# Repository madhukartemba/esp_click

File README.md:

# esp_click
This is a deep sleep ESP32 C6 push button device which transmits clicks via ESPNOW protocol. It uses an ESP32C6 microcontroller.

## Firmware build: broken RISC-V toolchain (PlatformIO)

ESP32-C6 uses the RISC-V toolchain (`riscv32-esp-elf-g++`). If the build fails with:

`sh: riscv32-esp-elf-g++: command not found` (exit 127)

the compiler package is missing, incomplete, or PlatformIO’s environment did not pick it up. From the firmware directory (`esp_click_firmware`), remove the toolchain and project build cache, then rebuild so PlatformIO re-downloads the toolchain:

```bash
cd esp_click_firmware
rm -rf .pio
rm -rf ~/.platformio/packages/toolchain-riscv32-esp
rm -rf ~/.platformio/tools/toolchain-riscv32-esp
pio run
```

Optional: remove all installed compiler packages (they reinstall on demand):

```bash
rm -rf ~/.platformio/packages/toolchain-*
```

Optional: prune unused PlatformIO packages:

```bash
pio system prune
```

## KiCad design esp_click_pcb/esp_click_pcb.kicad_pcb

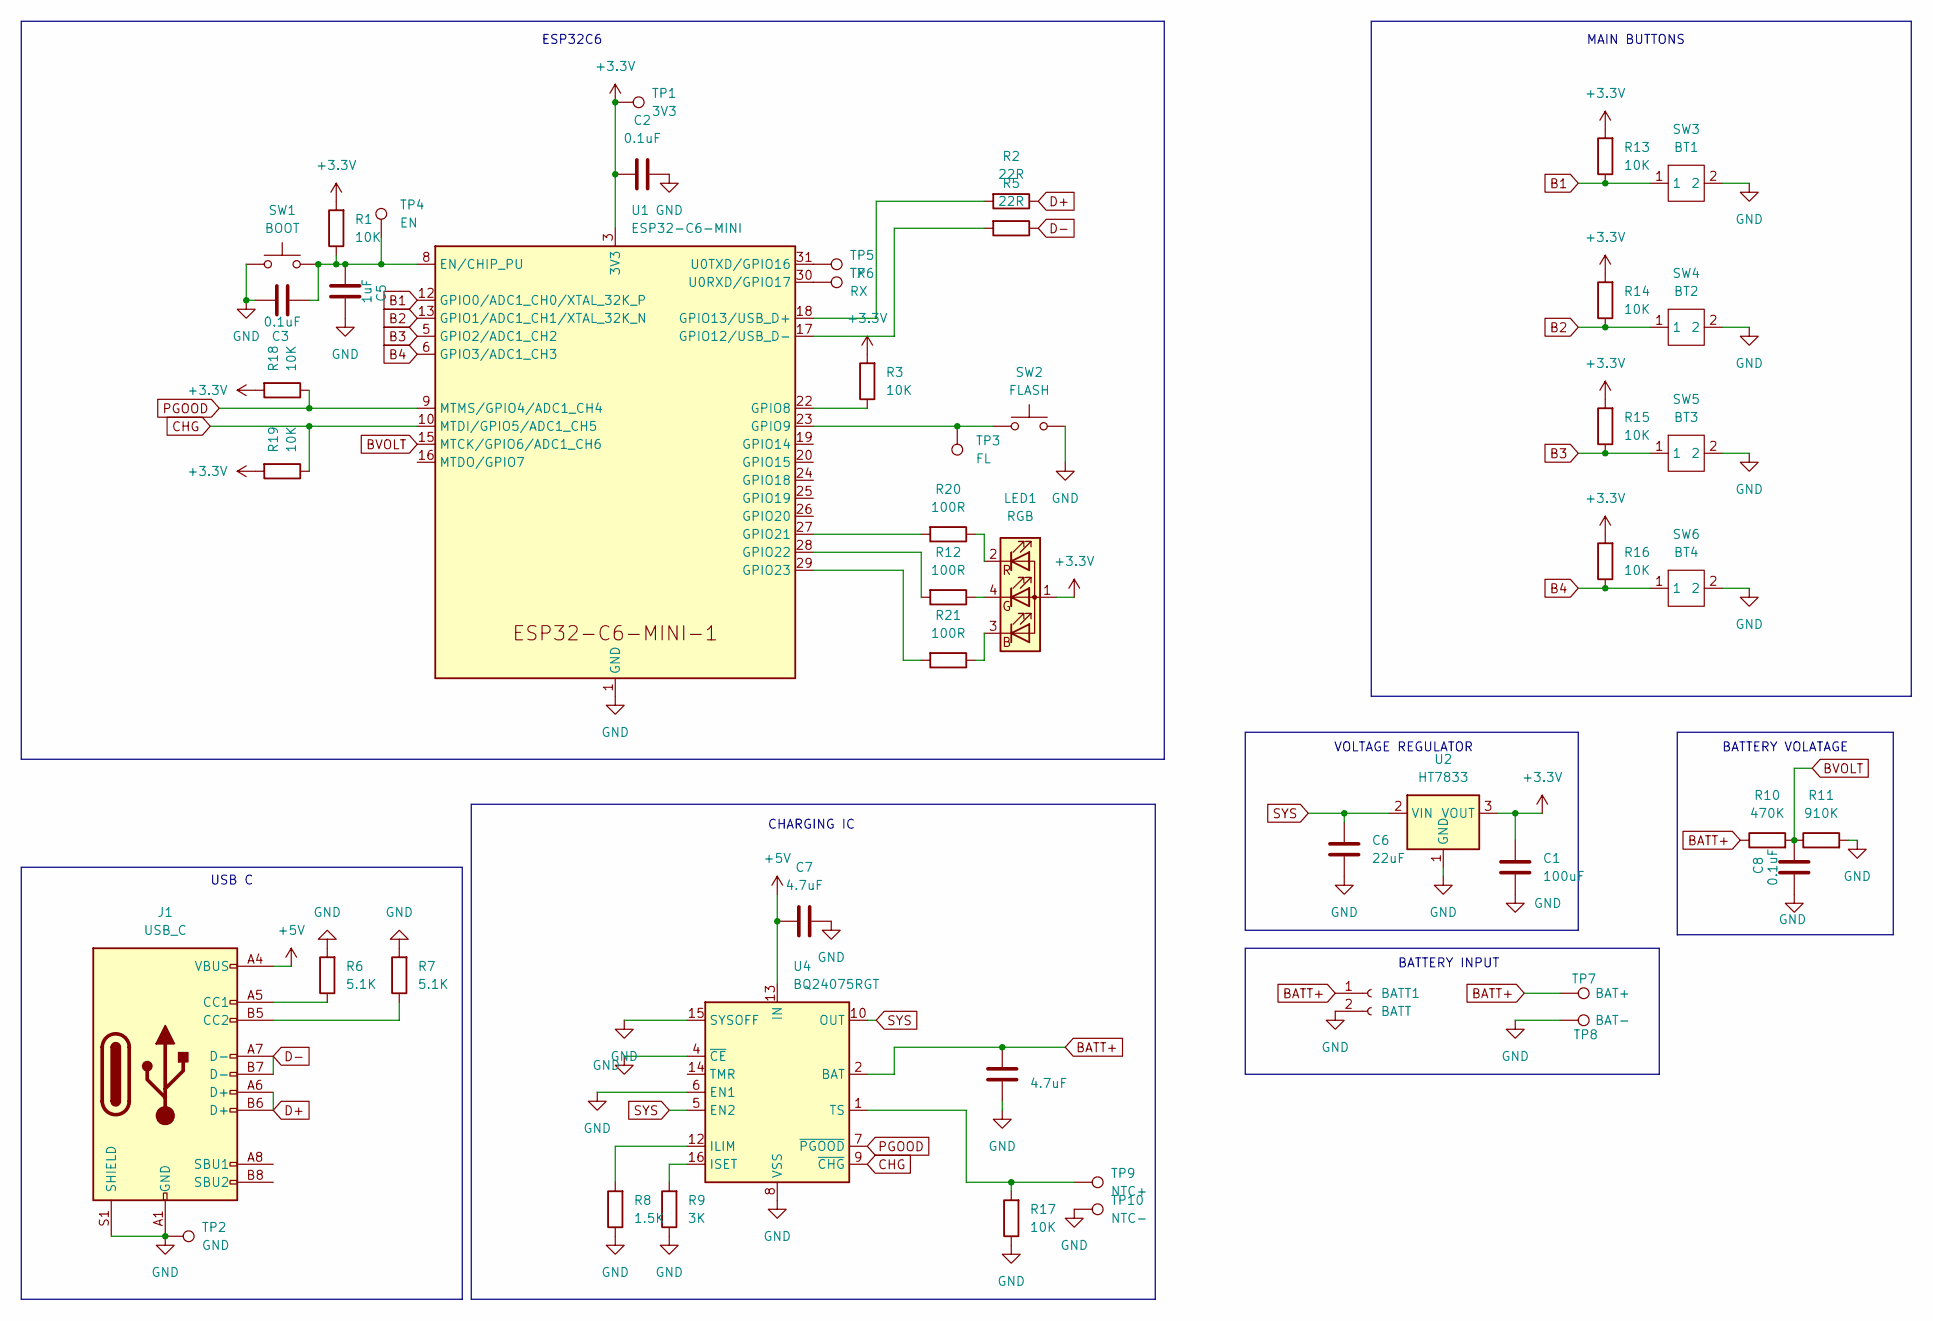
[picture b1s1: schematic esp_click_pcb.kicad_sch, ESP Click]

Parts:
BATT1: BATT; JST_SHL_SM02B-SHLS-TF_1x02-1MP_P1.00mm_Horizontal
C1: 100uF; C_0805_2012Metric
C2, C3, C8: 0.1uF; C_0603_1608Metric
C4, C7: 4.7uF; C_0805_2012Metric
C5: 1uF; C_0603_1608Metric
C6: 22uF; C_0805_2012Metric
J1: USB_C; USB_C_Receptacle_GCT_USB4110
LED1: RGB; XL-1615RGBC-RF
R1, R3, R13, R14, R15, R16, R17, R18, R19: 10K; R_0603_1608Metric
R2, R5: 22R; R_0603_1608Metric
R6, R7: 5.1K; R_0603_1608Metric
R8: 1.5K; R_0603_1608Metric
R9: 3K; R_0603_1608Metric
R10: 470K; R_0603_1608Metric
R11: 910K; R_0603_1608Metric
R12, R20, R21: 100R; R_0603_1608Metric
SW1: BOOT; TST-A002_0.6MM_BOSS
SW2: FLASH; TST-A002_0.6MM_BOSS
SW3: BT1; TS6643WS
SW4: BT2; TS6643WS
SW5: BT3; TS6643WS
SW6: BT4; TS6643WS
TP1: 3V3; TestPoint_Pad_D1.5mm
TP2: GND; TestPoint_Pad_D1.5mm
TP3: FL; TestPoint_Pad_D1.5mm
TP4: EN; TestPoint_Pad_D1.5mm
TP5: TX; TestPoint_Pad_D1.5mm
TP6: RX; TestPoint_Pad_D1.5mm
TP7: BAT+; TestPoint_Pad_D2.0mm
TP8: BAT-; TestPoint_Pad_D2.0mm
TP9: NTC+; TestPoint_Pad_D1.5mm
TP10: NTC-; TestPoint_Pad_D1.5mm
U1: ESP32-C6-MINI; ESP32-C6-MINI-1
U2: HT7833; SOT-89-3
U4: BQ24075RGT; VQFN-16-1EP_3x3mm_P0.5mm_EP1.6x1.6mm

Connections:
+3.3V: C1.1, C2.1, LED1.1 (A), R1.2, R3.2, R13.2, R14.2, R15.2, R16.2, R18.2, R19.2, TP1.1, U1.3 (3V3), U2.3 (VOUT)
+5V: C7.1, J1.A4 (VBUS), J1.A9 (VBUS), J1.B4 (VBUS), J1.B9 (VBUS), U4.13 (IN)
B1: R13.1, SW3.1, U1.12 (GPIO0/ADC1_CH0/XTAL_32K_P)
B2: R14.1, SW4.1, U1.13 (GPIO1/ADC1_CH1/XTAL_32K_N)
B3: R15.1, SW5.1, U1.5 (GPIO2/ADC1_CH2)
B4: R16.1, SW6.1, U1.6 (GPIO3/ADC1_CH3)
BATT+: BATT1.1, C4.1, R10.1, TP7.1, U4.2 (BAT), U4.3 (BAT)
BVOLT: C8.2, R10.2, R11.1, U1.15 (MTCK/GPIO6/ADC1_CH6)
CHG: R19.1, U1.10 (MTDI/GPIO5/ADC1_CH5), U4.9 (~CHG)
D+: J1.A6 (D+), J1.B6 (D+), R2.1
D-: J1.A7 (D-), J1.B7 (D-), R5.1
GND: BATT1.2, C1.2, C2.2, C3.2, C4.2, C5.2, C6.2, C7.2, C8.1, J1.A1 (GND), J1.A12 (GND), J1.B1 (GND), J1.B12 (GND), J1.S1 (SHIELD), R6.2, R7.2, R8.1, R9.1, R11.2, R17.1, SW1.1, SW2.2, SW3.2, SW4.2, SW5.2, SW6.2, TP2.1, TP8.1, TP10.1, U1.1 (GND), U1.2 (GND), U1.11 (GND), U1.14 (GND), U1.36 (GND), U1.37 (GND), U1.38 (GND), U1.39 (GND), U1.40 (GND), U1.41 (GND), U1.42 (GND), U1.43 (GND), U1.44 (GND), U1.45 (GND), U1.46 (GND), U1.47 (GND), U1.48 (GND), U1.49 (GND), U1.50 (GND), U1.51 (GND), U1.52 (GND), U1.53 (GND), U2.1 (GND), U4.4 (~CE), U4.6 (EN1), U4.8 (VSS), U4.15 (SYSOFF), U4.17 (VSS)
unnamed: J1.A5 (CC1), R6.1
unnamed: J1.B5 (CC2), R7.1
unnamed: LED1.3 (BK), R21.1
unnamed: LED1.4 (GK), R12.1
unnamed: LED1.2 (RK), R20.1
unnamed: C3.1, C5.1, R1.1, SW1.2, TP4.1, U1.8 (EN/CHIP_PU)
unnamed: R3.1, U1.22 (GPIO8)
unnamed: SW2.1, TP3.1, U1.23 (GPIO9)
unnamed: R5.2, U1.17 (GPIO12/USB_D-)
unnamed: R2.2, U1.18 (GPIO13/USB_D+)
unnamed: R20.2, U1.27 (GPIO21)
unnamed: R12.2, U1.28 (GPIO22)
unnamed: R21.2, U1.29 (GPIO23)
unnamed: TP6.1, U1.30 (U0RXD/GPIO17)
unnamed: TP5.1, U1.31 (U0TXD/GPIO16)
unnamed: R8.2, U4.12 (ILIM)
unnamed: R9.2, U4.16 (ISET)
unnamed: R17.2, TP9.1, U4.1 (TS)
PGOOD: R18.1, U1.9 (MTMS/GPIO4/ADC1_CH4), U4.7 (~PGOOD)
SYS: C6.1, U2.2 (VIN), U4.5 (EN2), U4.10 (OUT), U4.11 (OUT)

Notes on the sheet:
MAIN BUTTONS
CHARGING IC
BATTERY VOLATAGE
USB C
BATTERY INPUT
VOLTAGE REGULATOR
ESP32C6

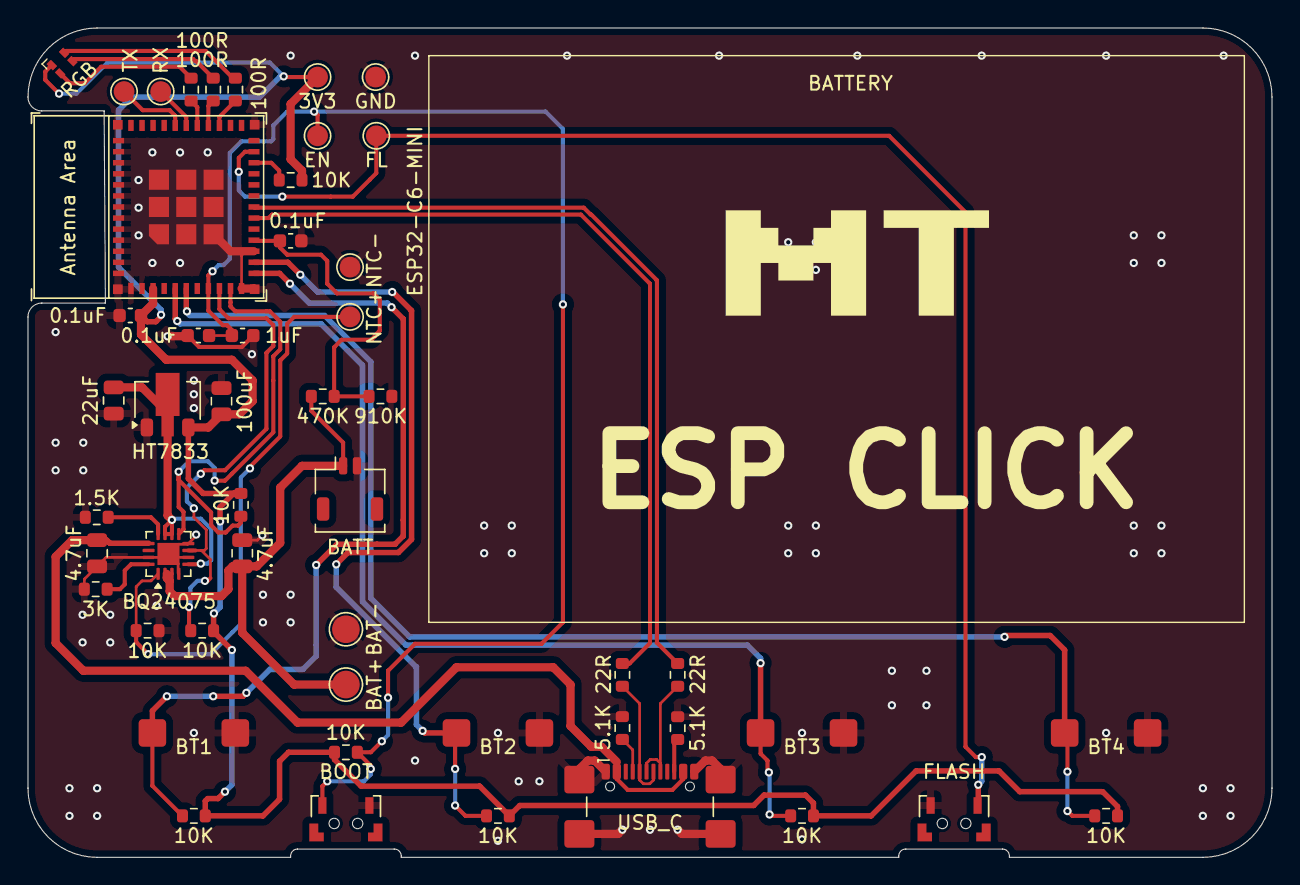
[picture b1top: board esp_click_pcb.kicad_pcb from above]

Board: 2 copper layers, 90.0 x 60.0 mm, 50 parts (0 on the bottom side), 32 nets.

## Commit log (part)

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2026-03-05 half complete pcb design
2026-03-05 pcb layout complete
2026-03-06 layout finished pcb
2026-03-06 use rgb led directly
2026-03-06 complete pcb design
2026-03-06 production build
2026-03-06 zip file
2026-03-06 remove zip
2026-03-08 ignore ds store
2026-03-08 initial code
2026-03-13 update pcb design, rev2
2026-03-14 rev 3
2026-03-15 add example code
2026-03-15 add io test file
2026-03-18 add 3d printing files
2026-03-18 add stl file
2026-03-18 change file name
2026-03-18 add brim
2026-03-19 update cap value
2026-03-19 add wall mount
2026-03-20 initial led lib
2026-03-20 add count support
2026-03-20 allow duplicates
2026-03-20 change fade speed
2026-03-20 working button class gi
2026-03-20 init button manager
2026-03-20 fix crash bug
2026-03-21 add task delay
2026-03-21 add base input class
2026-03-21 add analog input
2026-03-21 add monitor
2026-03-21 working battery manager
2026-03-21 add log
2026-03-21 add abstraction
2026-03-21 fix bugs
2026-03-21 remove instant battery read
2026-03-21 use threshold
2026-03-21 basic sleep manager
2026-03-21 add sleep manager
2026-03-21 working sleep
2026-03-21 remove log
2026-03-21 add deep sleep command for real :)
2026-03-21 register button pins
2026-03-21 fix pinmode flash bug
2026-03-21 remove enter
2026-03-22 add controller
2026-03-22 remove comment
2026-03-22 send message in callback
2026-03-22 add send logic
2026-03-22 first test
2026-03-22 add callbacks
2026-03-22 fix imports
2026-03-22 update controller
2026-03-23 working controller
2026-03-23 rearrange things
2026-03-23 rearrange
2026-03-23 change sleep default
2026-03-23 use broadcast for just finding the node
2026-03-23 change message struct;
2026-03-23 sleep in led blink
2026-03-24 add battery logging
2026-03-24 remove level change
2026-03-24 bug fix
2026-03-24 add logs
2026-03-24 fix bug
2026-03-24 fix led bug
2026-03-24 fix dreaded sleep bug
2026-03-24 add config file
2026-03-24 add config
2026-03-24 register wake up pin
2026-03-24 compiled code
2026-03-24 add missing files
2026-03-24 beautiful loop
2026-03-24 add led signals
2026-03-24 change led functions
2026-03-24 change led effect
2026-03-24 add status check
2026-03-24 change check
2026-03-24 change speed
2026-03-24 working voltage monitor
2026-03-24 fix status
2026-03-24 add low battery thresh
2026-03-24 working anim
2026-03-24 improve controller logic
2026-03-24 add space
2026-03-24 use rssi to find best node
2026-03-25 add wall mount 2
2026-03-26 fix typos
2026-03-26 rename
2026-04-16 vs code ext change
2026-04-16 add a base controller
2026-04-16 add ble controller
2026-04-16 disable espnow for now
2026-04-16 add zigbee
2026-04-16 Revert "add zigbee"
    This reverts commit f91387ed248439d0d1b91da58089eec314216af4.
2026-04-16 Revert "disable espnow for now"
    This reverts commit bdff6a1db95c68f1a96a91db538bf35517e9445f.
2026-04-16 remove ble controller
2026-04-18 change folder name
2026-04-18 add pairing methods
2026-04-18 implement encryption
2026-04-18 modify send message to reject unpaired messages
2026-04-18 add pairing button
2026-04-18 add rudimentary pairing logic
2026-04-18 add pairing retry attempty
2026-04-18 change pairing color
2026-04-18 increment counter in send msg
2026-04-18 add pairing nvs
2026-04-18 add session id
2026-04-19 skip register button as wakeup
2026-04-19 wipe config before pairing again
2026-04-19 updated main cpp
2026-04-19 update error codes
2026-04-19 add file assoc
2026-04-19 comments
2026-04-19 change colors
2026-04-19 update colors
2026-04-19 add encrypted ack
2026-04-19 spoof check
2026-04-19 make changes to ack
2026-04-19 add unpair req
2026-04-19 add msg
2026-04-19 add readme change
2026-04-20 add unpair anim
2026-04-20 change
2026-04-20 start pairnig on button press if unpaired
2026-04-20 magenta
2026-05-01 add 3d print files
2026-05-02 update sleep timeout
